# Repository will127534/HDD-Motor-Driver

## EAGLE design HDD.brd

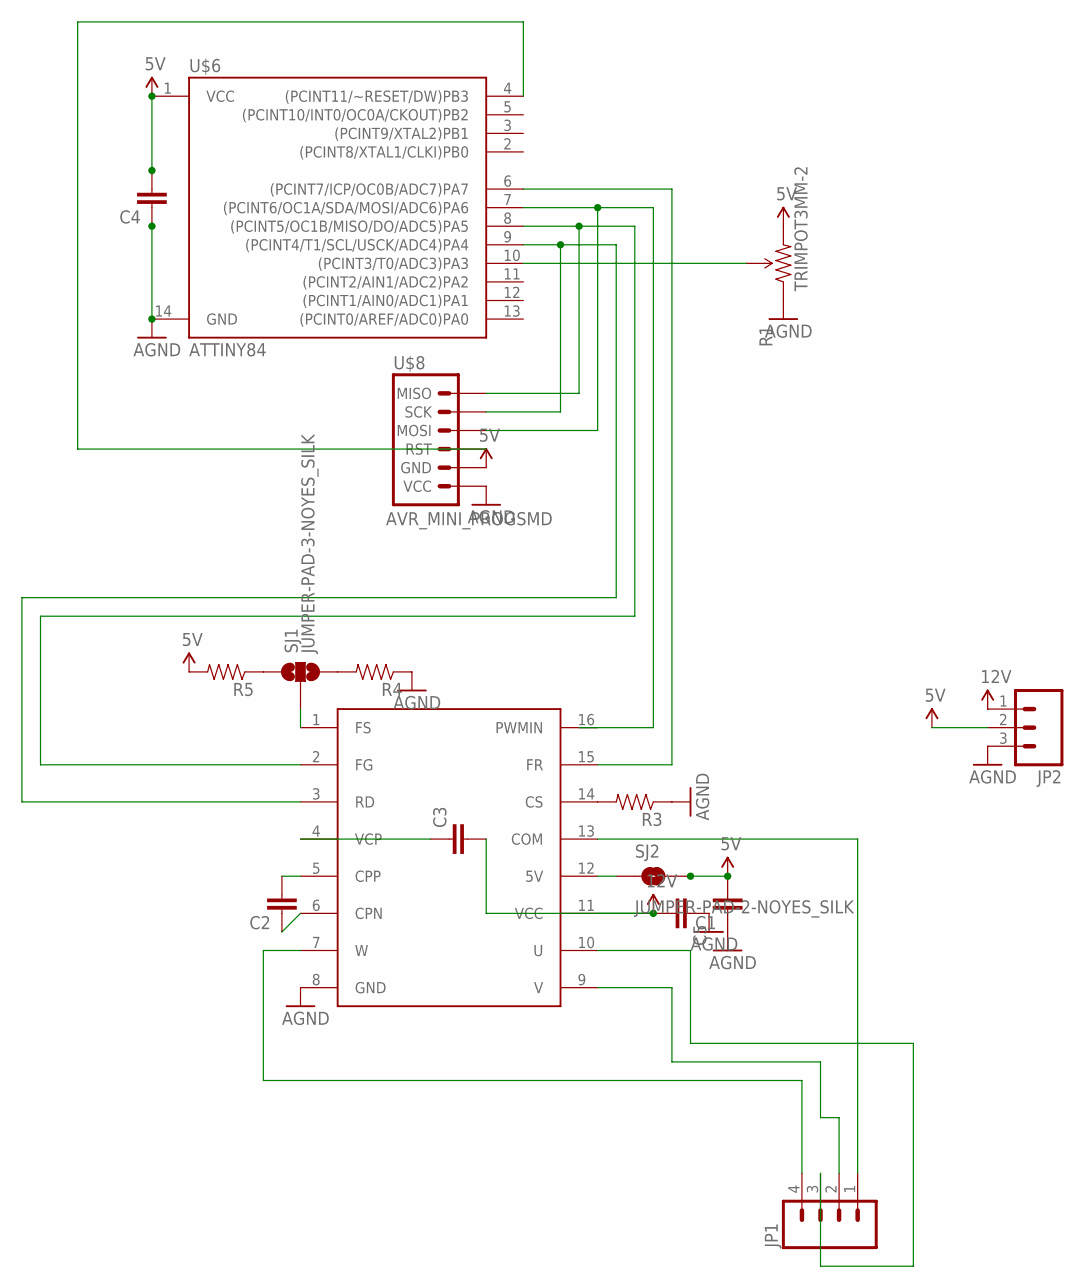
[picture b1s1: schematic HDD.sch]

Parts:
C1, C2, C3, C4, C5: CAP0805; 0805
JP1: M04LOCK; 1X04_LOCK
JP2: M03PTH; 1X03
R1: TRIMPOT3MM-2; TRIMPOT-3MM-2
R3, R4, R5: RESISTOR0805-RES; 0805
SJ1: JUMPER-PAD-3-NOYES_SILK; PAD-JUMPER-3-NO_YES_SILK
SJ2: JUMPER-PAD-2-NOYES_SILK; PAD-JUMPER-2-NO_YES_SILK
U$1: DRV11873; TSSOP-16
U$6: ATTINY84; SO14
U$8: AVR_MINI_PROGSMD; AVR_MINI_PROG

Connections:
5V: C1.2, C4.2, JP2.2, R1.3 (CW), R5.2, SJ2.2, U$6.1 (VCC), U$8.2 (GND)
12V: C3.2, C5.2, JP2.1, U$1.11 (VCC)
AGND: C1.1, C4.1, C5.1, JP2.3, R1.1 (CCW), R3.1, R4.1, U$1.8 (GND), U$6.14 (GND), U$8.1 (VCC)
unnamed: SJ2.1, U$1.12 (5V)
unnamed: C2.1, U$1.6 (CPN)
unnamed: C2.2, U$1.5 (CPP)
unnamed: U$1.2 (FG), U$6.8 ((PCINT5/OC1B/MISO/DO/ADC5)PA5), U$8.6 (MISO)
unnamed: C3.1, U$1.4 (VCP)
unnamed: U$1.3 (RD), U$6.9 ((PCINT4/T1/SCL/USCK/ADC4)PA4), U$8.5 (SCK)
unnamed: R3.2, U$1.14 (CS)
unnamed: JP1.1, U$1.13 (COM)
unnamed: JP1.3, U$1.10 (U)
unnamed: JP1.2, U$1.9 (V)
unnamed: JP1.4, U$1.7 (W)
unnamed: U$6.7 ((PCINT6/OC1A/SDA/MOSI/ADC6)PA6), U$8.4 (MOSI)
unnamed: U$1.15 (FR), U$6.6 ((PCINT7/ICP/OC0B/ADC7)PA7)
unnamed: SJ1.2, U$1.1 (FS)
unnamed: R4.2, SJ1.3
unnamed: R5.1, SJ1.1
unnamed: U$6.4 ((PCINT11/~RESET/DW)PB3), U$8.3 (RST)
unnamed: R1.2 (WIPER), U$6.10 ((PCINT3/T0/ADC3)PA3)

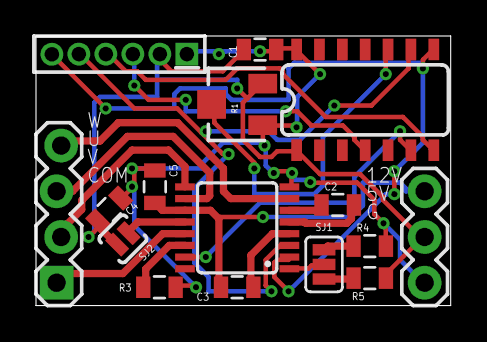
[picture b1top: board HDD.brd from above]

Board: 2 copper layers, 23.0 x 15.0 mm, 16 parts (0 on the bottom side), 21 nets.

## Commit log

2015-07-04 Upload PCB files

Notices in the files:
parts and their libraries:
SparkFun-Capacitors: Licensing: Creative Commons ShareAlike 4.0 International - https://creativecommons.org/licenses/by-sa/4.0
